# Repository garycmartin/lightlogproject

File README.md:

Lightlog Project
===============

A wearable, Open Source, ambient colour light tracker.

Installation
------------

To download data from Lightlog you'll need to set up your machine with some standard tools.

1) Install the device driver for the USB sync cable, install documentation steps, and driver are available at:

<http://www.picaxe.com/Software/Drivers/AXE027-USB-Cable-Driver/#download>

2) For Mac and Linux systems Python is usually already installed. If your using Windows and don’t have Python installed, there's a nice quick guide here if you need it. Please note that the scripts current require Python 2.7:

<http://www.anthonydebarros.com/2011/10/15/setting-up-python-in-windows-7/>

3) For Windows, make sure Python is added to your PATH variable, this is covered in the above guide.

```
C:\Python27;C:\Python27\Lib\site-packages\;C:\Python27\Scripts\;
```

4) Install pySerial module. The above guide also includes steps to add setuptools and pip, once you have them added you can type:

```shell
pip install pyserial
```

5) Download the lightlogdownload.py script from:

<https://raw.githubusercontent.com/garycmartin/lightlogproject/master/python/lightlogdownload.py>

…or make a local clone of the git repository. Github provides graphical git clients at <https://desktop.github.com> if needed.

6) Test that you can run the script ok by trying to use the command console or a shell window to check the script version:

```shell
python lightlogdownload.py --version
Version v0.13
```

7) Finally, plug in the serial cable, attach a Lightlog, and run the script...

Basic workflow
--------------

The usual work flow is to run:

```shell
python lightlogdownload.py --both
```

This will try to automatically find the connected serial port and communicate with Lightlog. Hold the button down on the Lightlog when it asks to establish the down link. The script will then download all logged data and save a .csv file of lux values containing red, green, blue, white, epoch seconds, and flags. The auto save file name includes the Light Log's unique ID, and if the save file already exists it will append any new data since the last download. This should make it easy to plug in each device, one after the other, and run the command each week to build up a continuous archive of data. Make sure you grab the data once a week (the default is one record a minute) or you'll have gaps in your data (at one record a minute, the memory holds 7days 14hrs worth of samples).

The epoch timestamps are seconds since 1st, Jan, 1970 (AKA Unix time, or POSIX time), you can quickly check a timestamp if needed with the below code snipped:

```shell
python -c 'import datetime; print (datetime.datetime(1970,1,1) + datetime.timedelta(seconds=1395802371))'
2014-03-26 02:52:51
```

For reference here's the download command's full arguments:

```
$ python lightlogdownload.py --help
usage: lightlogdownload.py [-h] [-p PORT] [-r] [-b] [--csv-header]
                           [--estimate]
                           [-f FILE | --stdout | --cal {2.5k,5k,10k} | --delay DELAY |
                           --phase PHASE | --sample SAMPLE | --status | --reset-memory |
                           --reset-cal | --reset-goal | --factory-reset | -v]
    
Download, convert and save data from Lightlog device. Without arguments data will be
saved to an auto-named csv file Light_Log_<device_ID>.csv in the current directory, if
the log file already exists, new data will be appended to the log.

optional arguments:
   -h, --help            show this help message and exit
   -p PORT, --port PORT  serial or COM port name
   -r, --raw             raw 10-bit sensor data, no conversion to lux scale
   -b, --both            auto saves two files, raw 10-bit sensor data and one
                         in lux
   --csv-header          outputs column header in first row of data (new log
                         files only)
   --estimate            force time estimate based on device period setting
                         rather than log time data
   -f FILE, --file FILE  save downloaded data to a named file
   --stdout              send data to console sandard output
   --cal {2.5k,5k,10k}   calibrate hardware to current lux light exposure
   --delay DELAY         fine tune device delay timing between samples 500-2000
                         (default 1000 = 10sec)
   --phase PHASE         set day phase 0-1439 in min (used for resetting daily
                         goal)
   --sample SAMPLE       number of samples per average 1-63 (default is 6
                         giving 1 record every minute)
   --status, -s          display device status data
   --reset-memory        reset memory pointer (for a fresh logging session)
   --reset-cal           reset lux calibration back to factory defaults
   --reset-goal          reset daily light goal
   --factory-reset       reset device back to all factory defaults, new unique
                         hardware ID will be generated (!!!)
   -v, --version         show download software version number and exit
```

Lightlogdownload.py script
--------------------------

When synching your devices I recommend using either the --raw or --both option, these generate a copy of the raw data before any calibration is applied (each device will generate a Light_Log_<device_ID>_raw.csv). If needed, this then allows you to control lux conversion/calibration using your own protocol, test equipment and math functions.

Without --raw or --both, you will only have the record of data after lux conversion has been applied using the code in Lightlogdownload.py. I have experimented with a number of fitted math curves to sample data sets, but none of them were satisfactory. My closest fit has been simply by interpolating between a set of lux vs. calibration data. The code is currently linearly interpolating between 16 calibration points.

Colour data
-----------

This python definition can be used if you want to convert the RGB values to colour temperature estimates:

```python
def calculate_colour_temp(colour):
   r = colour[0]
   g = colour[1]
   b = colour[2]
   n = ((0.23881 * r) + (0.25499 * g) + (-0.58291 * b)) / ((0.11109 * r) + (-0.85406 * g) + (0.52289 * b))
   cct = int(round(449 *  n ** 3 + 3525 *  n ** 2 + 6823.3 * n + 5520.33))
   return cct
```

Here’s another better commented example from Adafruit, where they use a library for the same sensor for Raspberry PI <https://github.com/adafruit/Adafruit-Raspberry-Pi-Python-Code/blob/master/Adafruit_TCS34725/Adafruit_TCS34725.py>

```python
def calculate_colour_temp2(colour):
   r = colour[0]
   g = colour[1]
   b = colour[2]

   # 1. Map RGB values to their XYZ counterparts.
   # Based on 6500K fluorescent, 3000K fluorescent
   # and 60W incandescent values for a wide range.
   X = (-0.14282 * r) + (1.54924 * g) + (-0.95641 * b)
   Y = (-0.32466 * r) + (1.57837 * g) + (-0.73191 * b) # also lux?
   Z = (-0.68202 * r) + (0.77073 * g) + ( 0.56332 * b)
    
   #2. Calculate the chromaticity co-ordinates
   xc = (X) / (X + Y + Z)
   yc = (Y) / (X + Y + Z)
    
   #3. Use McCamy's formula to determine the CCT
   n = (xc - 0.3320) / (0.1858 - yc)
    
   #Calculate the final CCT
   cct = (449.0 * n**3) + (3525.0 * n**2) + (6823.3 * n) + 5520.33
   return cct
```

For the raw data R, G, B, W, Time, Flag; R, G, B are 10-bit (0-1023) % of W, and W is a 10-bit exponential stored value of the original sensor reading (based on potentially two different 16-bit sensor gain exposures, depending on light brightness, see below).

The cases where you see W > R+G+B will be down to the 10-bit resolution the data is stored to memory. The sensor device samples 16-bit data, and may take two exposures of light (if needed) at different gains, one at x16, if that over exposes it then takes a second sample at x1 gain. It then takes the 16-bit W value and uses it to create a delta value for each R, G, B from W. W is then converted to 10-bits of data using a logarithmic scale so there is high detail for indoor lighting environments, but outdoor cases are still covered. R, G, B are then each converted to 10-bit (0-1023) % values of the W value (e.g. if the red sensor was 50% of the white sensor, R=511), this provides maximum resolution for R, G, B for both high values of W and low values of W.
 
The FIFO log buffer, with the default delay of one RGBW+flag record per minute, will last 7.5 days before data starts being ovberwritten. For the most accurate of log file timing it is best that some of your data overlaps your previous log, if found, lightlogdownload.py will use this data overlap to adjust sample deltas using the accurate system clock. If the data does not overlap lightlogdownload.py uses the devices sample rate to set a fixed time between records (most recent records will be the most accurate, with oldest records having most drift).
 
There are 64Kbytes available on the EEPROM for logging, each record is 6 bytes, giving 10922 available records 

You'll occasionally see something like this from lightlogdownload.py:

```
 Device day phase was 225min, now set to 227min
 Device delay tuning is set to 982 (984 suggested)
 ```
 
The first item refers to the day phase (1440min each day, local midnight=0min). The second appears if there was a reasonable number of new samples, it tells you the current timing delay used by this device, and its suggestion. You can see here it suggesting the device slows down a little to correct for the time drift. If you agree you can run:

```shell
$ python lightlogdownload.py --delay 984
```

It's not done automatically during a sync as it can't know how long you might have removed a battery for while replacing/changing. The delay value is already tuned at least a couple of times for the devices logging test data (over a couple of days duration minimum). Note that if your previous log file data overlaps with data in the device, lightlogdownload.py will adjust the sample timings between the start and end records using the real system time from your computer.

Battery life
------------

Expect 4 months (+/- a week) between battery changes under normal conditions. Be aware that very low temperatures will lower the battery voltage output.

If you want to have a safe margin of error, swap a battery once the script reports below 2.1V, you'll probably also notice the LEDs start to dim around this time as well.

The serial sync process and LED display are the most power hungry spikes that dip the voltage, so if the battery is low you may get a failed or no response message when trying to sync. Swapping out the battery for a new one, and trying to sync again should get all the data downloaded just fine.

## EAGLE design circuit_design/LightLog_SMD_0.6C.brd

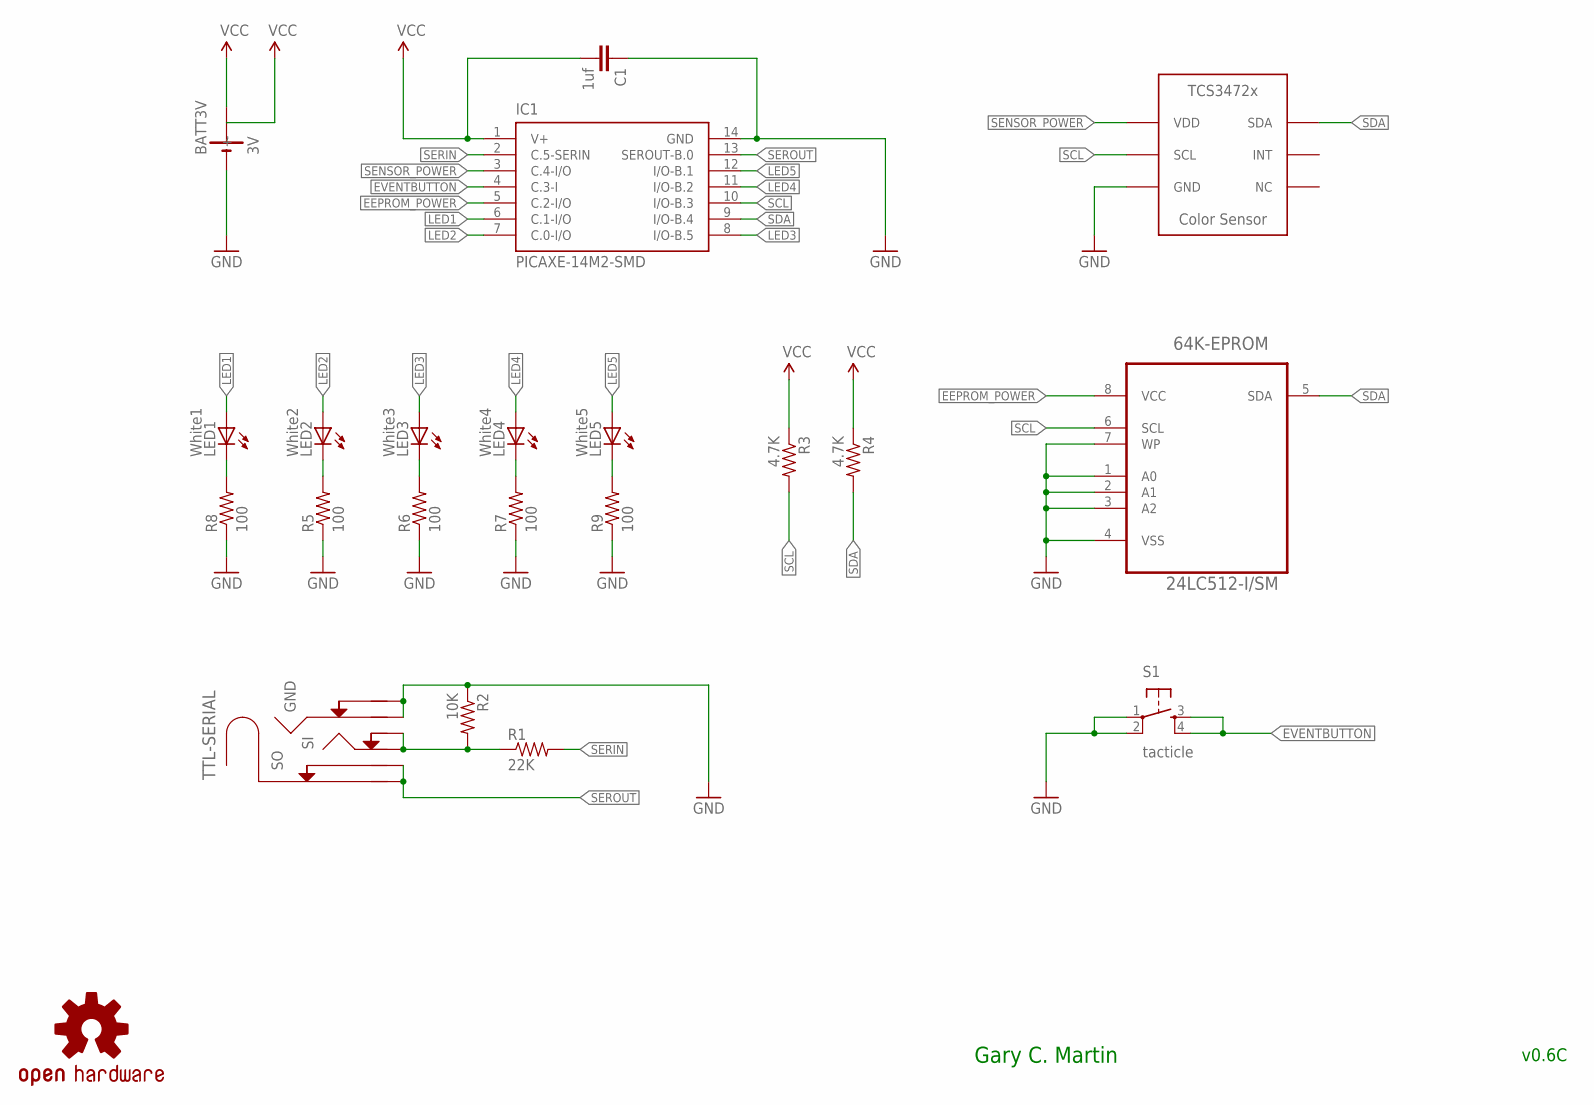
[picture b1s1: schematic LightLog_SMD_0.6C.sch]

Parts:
64K-EPROM: 24LC512-I/SM; SOIC127P794X203-8N
BATT3V: 3V; BAT-HLD-001-CR2032-SMD
C1: 1uf; 0805
IC1: PICAXE-14M2-SMD; SOIC14
LED1: White1; LED-1206
LED2: White2; LED-1206
LED3: White3; LED-1206
LED4: White4; LED-1206
LED5: White5; LED-1206
LOGO1: OSHW-LOGOS; OSHW-LOGO-S
R1: 22K; 0805
R2: 10K; 0805
R3, R4: 4.7K; 0805
R5, R6, R7, R8, R9: 100; 0805
S1: tacticle; TACTILE_SWITCH_SMD
TTL-SERIAL: 3-5MM-STEREO-SOCKET; 3-5MM-SMT
U$1: TCS3472; DUAL-FLAT-NO-LEAD-6PIN

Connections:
EEPROM_POWER: 64K-EPROM.8 (VCC), IC1.5 (C.2-I/O)
EVENTBUTTON: IC1.4 (C.3-I), S1.3, S1.4
GND: 64K-EPROM.1 (A0), 64K-EPROM.2 (A1), 64K-EPROM.3 (A2), 64K-EPROM.4 (VSS), 64K-EPROM.7 (WP), BATT3V.NEG (-), C1.1, IC1.14 (GND), R2.1, R5.1, R6.1, R7.1, R8.1, R9.1, S1.1, S1.2, TTL-SERIAL.5, TTL-SERIAL.6, U$1.3 (GND)
LED1: IC1.6 (C.1-I/O), LED1.A
LED2: IC1.7 (C.0-I/O), LED2.A
LED3: IC1.8 (I/O-B.5), LED3.A
LED4: IC1.11 (I/O-B.2), LED4.A
LED5: IC1.12 (I/O-B.1), LED5.A
unnamed: LED2.C, R5.2
unnamed: R1.1, R2.2, TTL-SERIAL.3, TTL-SERIAL.4
unnamed: LED3.C, R6.2
unnamed: LED4.C, R7.2
unnamed: LED5.C, R9.2
unnamed: LED1.C, R8.2
SCL: 64K-EPROM.6 (SCL), IC1.10 (I/O-B.3), R3.2, U$1.2 (SCL)
SDA: 64K-EPROM.5 (SDA), IC1.9 (I/O-B.4), R4.2, U$1.6 (SDA)
SENSOR_POWER: IC1.3 (C.4-I/O), U$1.1 (VDD)
SERIN: IC1.2 (C.5-SERIN), R1.2
SEROUT: IC1.13 (SEROUT-B.0), TTL-SERIAL.1, TTL-SERIAL.2
VCC: BATT3V.POS1 (+), BATT3V.POS2 (+), C1.2, IC1.1 (V+), R3.1, R4.1

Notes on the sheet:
Gary C. Martin
v0.6C

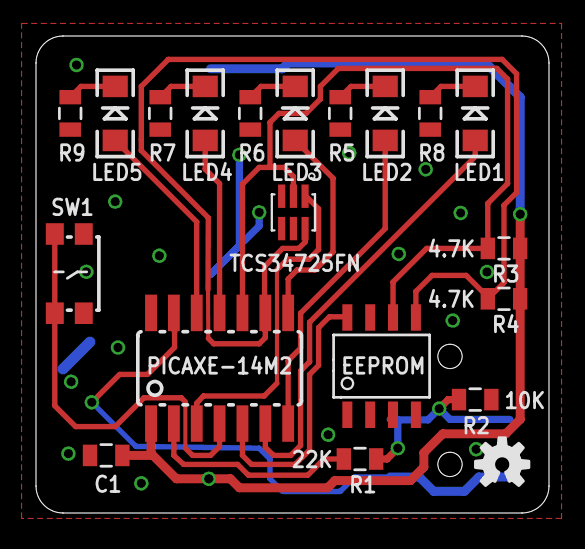
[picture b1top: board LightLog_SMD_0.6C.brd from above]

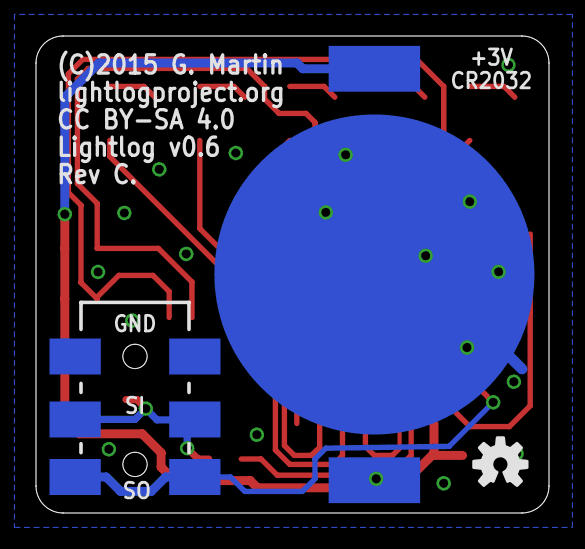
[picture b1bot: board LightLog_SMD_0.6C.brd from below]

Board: 2 copper layers, 28.5 x 26.5 mm, 23 parts (3 on the bottom side), 20 nets.

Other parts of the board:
LOGO2: OSHW-LOGOS; OSHW-LOGO-S

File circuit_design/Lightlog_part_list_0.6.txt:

=== Light Log SMD/SMT prototype v0.6 part list ===

Surface Mount PICAXE-14M2 [AXE017M2SM]
24AA512-I/SN 64Kb Microchip EEPROM SMT slim SOIC-8 3.9mm width package (with extra low 1.7V drop-out)
TCS34725FN ams RGBC Light to Digital Converters (with IR filter)
C1. 100nF decoupling capacitor Y5V0805CTTE105Z Ceramic Capacitors MLCC - SMD/SMT
LED1, LED2, LED3, LED4, LED5 white VAOL-S12WR4 Standard LED - SMD
SMT Battery Holder BAT-HLD-001 Linx CR2032
R1 22Kohm SG73S2ATTD2202F KOA Speer Thick Film Resistors SMD (limit current to serial in)
R2 10Kohm SG73P2ATTD1002F KOA Speer Thick Film Resistors SMD (stops serial in from floating)
R3, R4 4.7Kohm SG73S2ATTD4701F KOA Speer Thick Film Resistors SMD (pull-ups for I2C)
R5, R6, R7, R8, R9 50ohm-100ohm SG73P2ATTD1000F KOA Speer Thick Film Resistors SMD (LED current limit)
SW1 Tactile side button SW04440 MICROSWITCH, MINIATURE; Actuation Type:S KMS231G LFS, C&K COMPONENTS
3.5mm stereo socket MJ4435-R SMD/SMT [CON039SM]
USB to 3.5mm jack FTDI based serial cable [AXE027] (for Pic serial programming and data sync)
CR2032 Coin cell battery 3V (circuit operating range 2.1V-5.5V, 240mAh will last >4 months)

Where given, part numbers [in square brackets] can be found at techsupplies.co.uk. Many parts can also be found at other suppliers such as mouser.com, cpc.farnell.com and farnell.com. This prototype requires a custom 2 layer PCB board, LightLog_SMD_0.6_BRD, for assembly due to small SMD/SMT components.

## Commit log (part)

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2013-08-28 First commit of Light Log device firmware using PICAXE-08M2.
2013-09-05 Fixed (maybe) bugs with for loops near max int.
2013-09-28 Code refactor removing main for loop.
2013-11-02 Fixed i2c fault at higher than 8Mhz clock speeds & log data now dumped at 38400 baud.
2013-12-17 Testing for back reflection using LED blink & Hello? ping for auto serial sync.
2014-02-18 Code refactor and added firmware version to device status output.
2014-02-22 Tuning for blocked sensor detection (linked to new enclosure design).
2014-02-27 Wearable RGB + clear + button Light Log prototype schematic.
2014-02-27 Slide deck for NHS Lothian presentation 12th Sept 2013
2014-03-04 Removed CHANGE LOG now that source is in git.
2014-03-04 Added clear sensor light input to debugging output.
2014-03-08 Add first boot debug flag
2014-03-08 Improved first boot debug message
2014-03-08 Make sure averages are pre-filled at start of loop
2014-03-08 Remove unused byte variable
2014-03-08 Refactor variable usage to allow for transparent sensor
2014-03-08 Add in response to user button press
2014-03-09 Tidy up some comments
2014-03-09 Removed a scratch variable ready for transparent sensor use.
2014-03-10 Added a nap 0 to tight loop writing data to i2c
    Without a nap, a tight loop writing to i2c seems to skip a large number
    of writes. Took a long time to find this and not 100% sure why it works.
2014-03-10 Added a named symbol for a numerical value
2014-03-10 Renamed transparent to white
2014-03-10 Tidy up some formatting
2014-03-10 Fixed an indent for readability
2014-03-10 Deleted old commented code
2014-03-11 Add button press flag to replace the TBA.
2014-03-11 First boot Lux calibration and light goal tracking
2014-03-11 Remove auto status output on button press
2014-03-11 Make status data more machine readable.
2014-03-11 Rename LIGHT_COUNTER to DAY_PHASE for clarity
2014-03-11 Minimise status strings to save memory.
2014-03-11 Allow re-setting to the half day phase
2014-03-11 Removed a space from a status message
2014-03-11 Always send a display status as first part of a connection
2014-03-12 Version bump
2014-03-12 Update lux calibration data based on average of 7 Light Log
2014-03-12 More header text tweaking
2014-03-14 Removing eeprom zero erase code to save memory
    This is useful for memory debugging, but not really needed in
    production code.
2014-03-16 Flash pulsing timing behaviours
    Pulse speed will either be fast or slow. Fast for ‘this counts towards
    the goal’, slow for when light is not bright enough’.
2014-03-17 Fix data transfer and speed it up.
    Using 4 was a poor choice, needed to be a multiple of 6 to send all
    data correctly.
2014-03-22 Downloads and convert data from a Light Log <http://lightlogproject.org>
    Raw data bytes are downloaded from a Light Log device through a serial
    port and saved as a CSV file for easy processing with external tools.
    Time stamps use calculations based on the local systems time, so be
    aware your local clock should be reasonable accurate when downloading.
2014-03-22 Spend less time allowing MCU program downloads.
2014-03-22 Extend linear lux interpolation data points
2014-03-23 Comment cleanup.
2014-03-24 Tidy come comment formatting.
2014-03-24 Fix for --lux bug introduced in refactoring.
2014-03-24 Simplify calibration treatment of rgb to lux.
    The R, G, and B sensors are the same as for W, juts that they are
    behind a coloured gel filter. There was no need to try and clean up
    this data and make it add up to the W value for all cases.
2014-03-24 Improved behaviour for commands with no data block.
2014-03-24 Cleaned up console output for better cross-platform support.
    To avoid issues with non-ansi terminals some of the user feedback has
    been simplified to remove the need for cursor manipulation.
2014-03-25 Device status only displayed if requested.
    Keeps the console a little cleaner.
2014-03-25 Added auto name feature.
    Specifying —auto-name will save the data to the current directory with
    a name generated from the time epoch (last recorded time) and the Light
    Log device unique ID.
2014-03-25 Major cleanup and fix of command line arguments.
2014-03-26 Major refactor of the command line arguments and behaviour.
    Command now defaults to lux conversion, generating a output file based
    on the Light Log unique ID, appending only new data to the file if it
    exists already. Other options removed to try and simplify use.
2014-03-26 Remove #ifdef debug code.
    Not enough spare device program memory to enable these anymore so time
    to clean up the source.
2014-03-26 Remove leftover reference to start time register.
2014-03-27 Corrected push button switch to be down to GND.
    Micro controller supports internal pull up resistors, not pull down
    resistors.
2014-07-31 Ignore some file types
    Ignore some source code editor file noise.
2014-07-31 New part list for SMD/SMT board
    Prototype 0.6 uses a custom 2 layer PCB board and surface mount
    components, this lists the parts required to populate the board.
2014-08-17 Tweaks to cpu speed changes
2014-08-17 Avoid case where button is held down
    Only allow the button to be held down for 3 cycles to prevent case
    where power may be drained if button is permanently held down.
2014-08-17 Define connection speed more clearly
2014-08-21 Display gap duration between logs for missing data
    If data hasn’t been downloaded soon enough (before the history starts
    to be overwritten), display the amount of time in minutes lost.
2014-08-27 Don't fail if header is missing some stat
    Header stat data can be prone to change from time to time so don’t bail
    unless some critical data is missing.
2014-09-10 Lux scales update
    New visual lux graph line positions for 2.5k, 5k, and 10k lux from the
    new sensor and data format.
2014-09-10 Remove un-needed 20K calibration data
2014-09-10 Refactor goal_update to a separate routine
2014-09-10 Remove 20k lux calibration comms and function
2014-09-10 Eagle CAD board and schematic for SMT v0.6
2014-09-10 Initial enclosure work
    Blocking out volume needed for hand build prototype
2014-09-10 Revert 9381a92..73068e1
    This rolls back to commit 9381a92e6241ea29a37aab7485646c7582f03154.
2014-09-10 Wrong branch...
2014-09-10 Circular case with clip
2014-09-10 New fitted square case
2014-09-10 New higher res internal volume shape
2014-09-10 Added slot for fastener
2014-09-10 Added round window for LED location
2014-09-10 More small size tweaks
2014-09-10 Solid case without magnetic strap
    Two separate sections for ridged XT material, separate badge clip can
    be used to attach
2014-09-10 Clip fastening improvements
2014-09-10 Case 48
2014-09-10 Case 53
2014-09-10 Case 59
2014-09-10 Case 61
2014-09-10 Case 67
2014-09-10 Case 72
2014-09-10 Case 77
2014-09-10 Spacer for LDR component
    Spacer to go behind hand soldered LRD sensors to position them close to
    the case sensor ‘window’ for maximum exposure.
2014-09-10 Case 89
2014-09-10 Case 93
    Soft, flexible all in one case
2014-09-10 Case 104
2014-09-10 Case 113
2014-09-10 Case 119
2014-09-10 Case 123
2014-09-10 Case 131
2014-09-10 Case 142
2014-09-10 Case 151
2014-09-10 Case 157 for new SMT board
    First version of thin, single part case for the custom SMT board.
2014-09-10 Case 160
2014-09-10 Channel data scaled to better fill 10 bit range
    Data is now scaled to better fit the 10bit space (previously was 1/16
    short of 0x1111111111 max). Refactor of bit_compress procedures to save
    some memory and make code cleaner. Lux calibration updated to match new
    scale.
2014-09-15 Fix bug introduced in daily light goal logic
    Program flow changes were going through test that were previously
    avoided after clobbering tmp2_word with some other work value causing
    goal to be indicated as reached incorrectly.
2014-10-06 Bug fix for incorrect compressing
    A band of low data was getting scrambled by a simple test optimisation
    mistake.
2014-10-06 Debug output for phase data sync state
2014-10-14 Convert to lux early
    For data scent search to work on both raw and lux logs, the conversion
    to lux needed to be done earlier or the lux search would fail and
    fallback to time stamp based appends.
2014-10-27 Updates to internal device timing
2014-10-27 Ignore Pycharm junk files
2014-12-24 New SMD 0.7B board revision files
    Removes unnecessary pull-up resistor for BLE reset pin; adds P-Type
    MOSFET to provide enough current for BLE on power spike from a micro
    output pin; wider traces where possible; LED outputs nudged down a
    little; more GND vias
2015-02-12 Lightlog v0.6 REV C board
    Small changes to improve ease of reflow and applying solder paste
    stencil masking, only two components need to be hand soldered to the
    back of the board (battery holder and data sync socket).
2015-03-10 Refactoring and feature additions to command-line argument. Removed the cmd argument and separated out its individual command options into their own separate arguments to make documentation clearer a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
2015-03-10 New lux calibration for soft cases with the larger sensor window.
2015-03-10 Remove un-needed extra user output.
2015-03-10 Version number bump to v0.13
2015-03-10 Split up firmware to make use of double the available program memory (slot0 & slot1 each allow 2048 bytes)
2015-03-11 Clean-up comments and replace stray tabs with spaces.
2015-03-11 Save some program bytes.
2015-03-11 Refactor main sample loop and remove code now accessed via slot 1. A large chunk of the main sample loop is now over in slot 1 and a refactor was required. This patch also adds the ability to customi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
2015-03-11 Refactor for slot 0 vs slot 1 program switching and deal with edge cases.
2015-03-11 Replaced some math with inc.
2015-03-11 Add animation to 100% goal by fast or slow blinking LEDs based on current light level. Previously all LED would be lit once the daily goal was reached; now they all blink slowly if the light is below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
2015-03-11 Version bump to firmware 21 (for the change in format for colour data) and hardware 5 (for the soft cases with the larger sensor window).
2015-06-02 Move all symbol definitions for clarity
    All symbol definitions have been moved to the top of the source, just
    below the compiler directives, for clarity. Symbols are defined at
    compile time not run time.
2015-06-23 Fix issue when appending to a log file is less than 6 rows long
    Fall back for when there are less than 6 rows of data in a previous
    log. 6 rows are used for matching the start/end when appending new data
    and correcting for device time drift. If less than 6 rows the new data
    will be appended based on device time offset estimation.
2015-08-01 Correct memory wrapping bug
    Memory would wrap one record too soon, but would download that extra
    un-written record during a sync once memory was full resulting in a
    record with all values of 1023 (including the flag so it would look
    like an intermittent reboot).
2015-08-01 Cleanup changes in micro frequency
2015-08-01 Improve 10bit scaling and fix bad conversion edge case
    With more memory available, a larger set of test cases provides
    smoother conversions. It also fixed two narrow edge cases where an
    incorrect conversion could happen due to an integer word overflow.
2015-08-01 Allow user to force using time estimates
    This allows some edge and test cases where a user may not want to have
    the system try and interpolate to a previously logged data time stamp.
2016-02-09 Version bump to firmware 22

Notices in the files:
circuit_design/LightLog_SMD_0.6C.brd:
(C)2015 G. Martin
CC BY-SA 4.0
parts and their libraries:
SparkFun-Aesthetics: Licensing: CC v3.0 Share-Alike You are welcome to use this library for commercial purposes.
SparkFun-Aesthetics: Released under the Creative Commons
SparkFun-Aesthetics: http://creativecommons.org/licenses/by-sa/3.0
